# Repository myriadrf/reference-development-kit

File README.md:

# Myriad-RF Hardware

This repository contains the [Myriad-RF](http://myriadrf.org/) reference hardware designs for Lime Microsystem's LMS6002D and LMS7002M transceivers, plus LMS8001 up/down converter, in PDF and [KiCad](http://www.kicad.org) formats, along with the associated firmware.

## Contents

The directory structure for the hardware designs is as follows:

      docs/                      - platform documentation

      <project>/hardware/<version>/
          BOM/                   - bill of materials spreadsheet
          Gerbers/               - Gerber CAM files
          KiCAD/                 - KiCAD schematic and layout files
          Manufacturing/         - Additional manufacturing information
          PDF/                   - Schematic and layout PDFs
          Reports/               - DRC, ERC and drill reports

### Documentation

* RFDIO Connector Specification

The Myriad-RF Radio Frequency Digital Input Output (RFDIO) connector specification defines the electrical and mechanical properties of a high speed card interface for Field Programmable Gate Array (FPGA) based carrier boards. This specification ensures interoperability between carrier (mother) boards and add-on (daughter) RF cards.

*Please note that this needs to be updated with details of the connector specification used by the micro series of boards.*

### Myriad-RF 1 module (myriadrf-1)

Hardware design files for the LMS6002-based Myriad-RF 1 RF module.

Note that there are two versions of the design: one with vias in pads, and another with them off.

### DE0-Nano Interface (de0nano-interface)

Hardware design files and firmware sources (FPGA HDL + Cypress FX2 code) for the DE0-Nano interface that is used with the original Myriad-RF 1 module.

### Zipper Interface (zipper)

This interface allows the Myriad-RF 1 to be used with FPGA development boards that have either a HSMC or FMC connector.

*Note that v1 of the hardware design was not made generally available.*

### uMyriadRF-6002 (umyriadrf-6002)

LMS6002 version of the micro form factor RF module.

### uMyriadRF-7002 (umyriadrf-7002)

LMS7002 version of the micro form factor RF module.

### MyriadRF-8001 (myriadrf-8001)

LMS8001 Companion.

## Licensing

### Hardware

The hardware designs are licensed under a Creative Commons Attribution 3.0 Unported licence.

*Note: The Myriad-RF 1 and DE0-Nano Interface hardware designs were initially published under the Creative Commons Attribution-ShareAlike 3.0 Unported licence. As of 30th September 2013 these have been re-licensed under the more permissive Creative Commons Attribution 3.0 Unported licence.*

### Firmware

For details of firmware licensing please see the associated COPYING file(s).

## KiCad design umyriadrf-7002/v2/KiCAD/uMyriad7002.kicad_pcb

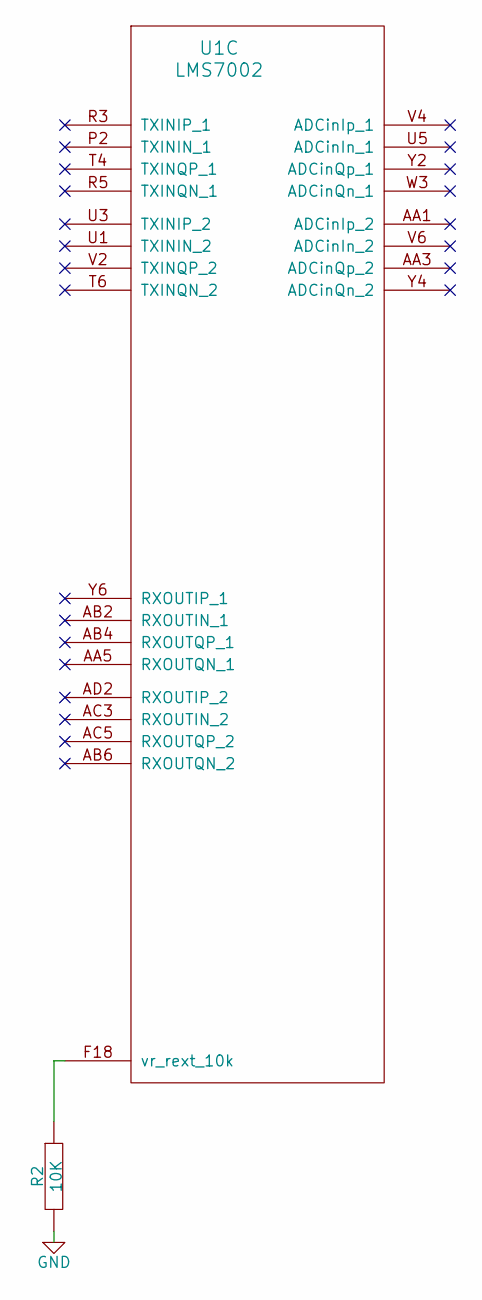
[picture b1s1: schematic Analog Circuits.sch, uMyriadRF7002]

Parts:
R2: 10K_0402; SMD0402; Manufacturer Part Number RMCF0402FT10K0
U1: LMS7002; aQFN-261

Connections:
GND: R2.2; also elsewhere on the board
unnamed: R2.1, U1.F18 (vr_rext_10k)

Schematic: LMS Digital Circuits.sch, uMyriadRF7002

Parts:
C13, C14, C15: 1UF_0402; SMD0402; Manufacturer Part Number CC0402ZRY5V5BB105
C22: 10PF_0402; SMD0402; Manufacturer Part Number CC0402JRNPO9BN100
J1: 100-PIN_CONNECTOR_3MMHEIGHT; 100-PIN_CONNECTOR; Manufacturer Part Number DF40HC(3.0)-100DS-0.4V(58)
R1, R11, R19, R20, R21, R22, R24: 10K_0402; SMD0402; Manufacturer Part Number RMCF0402FT10K0
R25, R26, R27, R28: 47R_0402; SMD0402; Manufacturer Part Number RC0402FR-0747RL
R29, R39: 2K2_0402; SMD0402; Manufacturer Part Number RC0402FR-072K2L
U1: LMS7002; aQFN-261
U6: 24FC512; 8-TSSOP; Manufacturer Part Number 24FC512-I/ST
U8: 24FC64F; 8-TSSOP; Manufacturer Part Number 24FC64F-I/ST

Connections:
+1.8V: J1.21, J1.22, J1.23, J1.24; also elsewhere on the board
+1.25V: J1.83, J1.84, J1.85, J1.86; also elsewhere on the board
+3.3V: C13.1, C14.1, C15.1, J1.17, J1.18, J1.19, J1.20, R11.1, R19.1, R20.1, R22.1, R24.1, R29.1, R39.1, U6.1 (A0), U6.2 (A1), U6.3 (A2), U6.8 (Vcc), U8.8 (Vcc); also elsewhere on the board
DIG_RST: J1.44, R21.2, U1.V30 (DIG_RST)
DIQ1_D0: J1.74, U1.AG31 (DIQ0_1)
DIQ1_D1: J1.76, U1.AF30 (DIQ1_1)
DIQ1_D2: J1.79, U1.AF34 (DIQ2_1)
DIQ1_D3: J1.72, U1.AE31 (DIQ3_1)
DIQ1_D4: J1.70, U1.AD30 (DIQ4_1)
DIQ1_D5: J1.78, U1.AC29 (DIQ5_1)
DIQ1_D6: J1.77, U1.AE33 (DIQ6_1)
DIQ1_D7: J1.75, U1.AD32 (DIQ7_1)
DIQ1_D8: J1.68, U1.AC31 (DIQ8_1)
DIQ1_D9: J1.73, U1.AC33 (DIQ9_1)
DIQ1_D10: J1.80, U1.AB30 (DIQ10_1)
DIQ1_D11: J1.66, U1.AB32 (DIQ11_1)
DIQ2_D0: J1.52, U1.H30 (DIQ0_2)
DIQ2_D1: J1.49, U1.J31 (DIQ1_2)
DIQ2_D2: J1.50, U1.K30 (DIQ2_2)
DIQ2_D3: J1.51, U1.K32 (DIQ3_2)
DIQ2_D4: J1.56, U1.L31 (DIQ4_2)
DIQ2_D5: J1.54, U1.K34 (DIQ5_2)
DIQ2_D6: J1.58, U1.M30 (DIQ6_2)
DIQ2_D7: J1.53, U1.M32 (DIQ7_2)
DIQ2_D8: J1.60, U1.N31 (DIQ8_2)
DIQ2_D9: J1.55, U1.N33 (DIQ9_2)
DIQ2_D10: J1.64, U1.P30 (DIQ10_2)
DIQ2_D11: J1.62, U1.P32 (DIQ11_2)
ENABLE_IQSEL1: J1.67, U1.Y32 (IQSEL_Enable_1)
ENABLE_IQSEL2: J1.59, U1.R33 (IQSEL_Enable_2)
FCLK1: J1.69, U1.AA33 (FCLK1)
FCLK2: J1.61, U1.R29 (FCLK_2)
FPGA_LMS_CS: J1.38, R25.2
FPGA_SPI_MISO: J1.37, R28.2
FPGA_SPI_MOSI: J1.36, R27.2
FPGA_SPI_SCK: J1.40, R26.2
GND: C13.2, C14.2, C15.2, C22.2, J1.1, J1.2, J1.3, J1.4, J1.5, J1.6, J1.7, J1.8, J1.9, J1.10, J1.15, J1.16, J1.25, J1.26, J1.27, J1.28, J1.29, J1.30, J1.31, J1.32, J1.33, J1.34, J1.81, J1.82, J1.87, J1.88, J1.90, J1.91, J1.92, J1.93, J1.94, J1.95, J1.96, J1.97, J1.98, J1.99, J1.100, R1.1, R21.1, U6.4 (Vss), U6.7 (WP), U8.1 (A0), U8.2 (A1), U8.3 (A2), U8.4 (Vss), U8.7 (WP); also elsewhere on the board
GPIOn: J1.43; also elsewhere on the board
GPIOp: J1.41; also elsewhere on the board
G_PWR_DWN: J1.46, R24.2, U1.U33 (G_PWR_DWN)
MCLK1: J1.71, U1.AB34 (MCLK1)
MCLK2: J1.57, U1.P34 (MCLK_2)
unnamed: R25.1, U1.D28 (SEN)
unnamed: R28.1, U1.F28 (SDO)
unnamed: R27.1, U1.F30 (SDIO)
unnamed: C22.1, R26.1, U1.C29 (SCLK)
unnamed: R29.2, U1.D26 (SDA), U6.5 (SDA), U8.5 (SDA)
unnamed: R39.2, U1.C27 (SCL), U6.6 (SCL), U8.6 (SCL)
RESET: J1.42, R22.2, U1.E27 (RESET)
RXPLL_CLK: J1.89, U1.AM24 (RxPLL_CLK)
RX_EN: J1.47, R11.2, U1.V34 (RX_EN)
TXNRX1: J1.65, R19.2, U1.V32 (TXNRX1)
TXNRX2: J1.63, R1.2, U1.U31 (TXNRX2)
TXPLL_CLK: J1.35, U1.E5 (TxPLL_CLK)
TX_EN: J1.48, R20.2, U1.U29 (TX_EN)

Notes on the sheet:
+5V

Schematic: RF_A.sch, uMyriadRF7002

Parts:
C1, C2, C16, C220, C221: 100NF_0402; SMD0402; Manufacturer Part Number CC0402ZRY5V7BB104
C3, C7, C32: 1PF_0402; SMD0402; Manufacturer Part Number C1005C0G1H010B050BA
C6: 0.5PF_0402_NF; SMD0402; Manufacturer Part Number CC0402CRNPO9BNR50
C9, C10: 4.7PF_0402; SMD0402; Manufacturer Part Number GRM1555C1H4R7BA01D
C17, C222: 22PF_0402; SMD0402; Manufacturer Part Number CC0402JRNPO9BN220
C33, C218, C219, C223: 100PF_0402; SMD0402; Manufacturer Part Number CC0402JRNPO9BN101
EK1: SHIELD_30X25MM; shield_30x25mm
L3, L9: 12NH_0402_NF; IND_0402; Manufacturer Part Number 0402HP-12NX_LU
L4: 3.9NH_0402; IND_0402; Manufacturer Part Number 0402HP-3N9XGLU
L7, L8: 8.2NH_0402; IND_0402; Manufacturer Part Number 0402HP-8N2XJLU
R9, R12: 0R_0805; SM0805; Manufacturer Part Number RC0805JR-070RL
R44: 10K_0402; SMD0402; Manufacturer Part Number RMCF0402FT10K0
T1, T2: TR_TCM1-63AX+; TCM1-63AX+; Manufacturer Part Number TCM1-63AX+
T5: TR_TC1; TC1-1-13MA+; Manufacturer Part Number TC1-1-13MA+
U1: LMS7002; aQFN-261; Manufacturer Part Number LMS7002M
U7: PE4245; 6-DFN_PE4245; Manufacturer Part Number 4245-52
X1, X3: U.FL; Manufacturer Part Number 0734120110

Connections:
+1.8V: C1.1, C2.1, R9.1, R12.1; also elsewhere on the board
+3.3V: C16.1, C17.1, C221.1, C222.1, L9.1, R44.2, U7.4 (Vdd3V); also elsewhere on the board
GND: C1.2, C2.2, C16.2, C17.2, C220.2, C221.2, C222.2, EK1.1, T1.1, T1.2, T1.5, T2.1, T2.2, T2.5, T5.2, T5.4, T5.5, U1.AK12 (RF_gnd), U1.AL13 (RF_gnd), U7.2 (GND), X1.2 (GND), X3.2 (GND); also elsewhere on the board
GPIOp: C220.1, R44.1, U7.5 (CTRL); also elsewhere on the board
unnamed: C218.2, U7.3 (RF1)
unnamed: C223.1, U7.6 (RFC)
unnamed: C218.1, T5.6
unnamed: C3.2, C7.1, T1.4
unnamed: C7.2, C32.2, T1.6
unnamed: C219.1, T2.3
unnamed: C219.2, U7.1 (RF2)
unnamed: C223.2, L9.2, X1.1 (RF)
unnamed: L7.1, R9.2
unnamed: L8.1, R12.2
unnamed: C33.1, T1.3
unnamed: C9.1, L3.1, U1.AK14 (RXRF1_p_h)
unnamed: C10.1, L3.2, U1.AJ15 (RXRF1_n_h)
unnamed: C9.2, L4.1, T2.4
unnamed: C10.2, L4.2, T2.6
unnamed: C6.2, C32.1, L8.2, U1.A7 (TXRF1_1n)
unnamed: C33.2, X3.1 (RF)
unnamed: C3.1, C6.1, L7.2, U1.B8 (TXRF1_1p)
unnamed: T5.3, U1.AM12 (RXRF1_n_l)
unnamed: T5.1, U1.AN11 (RXRF1_p_l)

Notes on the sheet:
TXOUT_A
GPIO 0 - RF1 1 - RF2
RXIN_A

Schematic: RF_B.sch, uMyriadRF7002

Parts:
C11, C12: 4.7PF_0402; SMD0402; Manufacturer Part Number GRM1555C1H4R7BA01D
C18, C38, C39, C233, C234: 100NF_0402; SMD0402; Manufacturer Part Number CC0402ZRY5V7BB104
C19, C235: 22PF_0402; SMD0402; Manufacturer Part Number CC0402JRNPO9BN220
C40, C42, C43: 1PF_0402; SMD0402; Manufacturer Part Number C1005C0G1H010B050BA
C41: 0.5PF_0402_NF; SMD0402; Manufacturer Part Number CC0402CRNPO9BNR50
C45, C231, C232, C236: 100PF_0402; SMD0402; Manufacturer Part Number CC0402JRNPO9BN101
EK2: SHIELD_30X25MM; shield_30x25mm
L5, L14: 12NH_0402_NF; IND_0402; Manufacturer Part Number 0402HP-12NX_LU
L6: 3.9NH_0402; IND_0402; Manufacturer Part Number 0402HP-3N9XGLU
L12, L13: 8.2NH_0402; IND_0402; Manufacturer Part Number 0402HP-8N2XJLU
R13, R14: 0R_0805; SM0805; Manufacturer Part Number RC0805JR-070RL
R45: 10K_0402; SMD0402; Manufacturer Part Number RMCF0402FT10K0
T3, T4: TR_TCM1-63AX+; TCM1-63AX+; Manufacturer Part Number TCM1-63AX+
T6: TR_TC1; TC1-1-13MA+; Manufacturer Part Number TC1-1-13MA+
U1: LMS7002; aQFN-261
U9: PE4245; 6-DFN_PE4245; Manufacturer Part Number 4245-52
X2, X4: U.FL; Manufacturer Part Number 0734120110

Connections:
+1.8V: C38.1, C39.1, R13.1, R14.1; also elsewhere on the board
+3.3V: C18.1, C19.1, C234.1, C235.1, L14.1, U9.4 (Vdd3V); also elsewhere on the board
GND: C18.2, C19.2, C38.2, C39.2, C233.2, C234.2, C235.2, EK2.1, R45.2, T3.1, T3.2, T3.5, T4.1, T4.2, T4.5, T6.2, T6.4, T6.5, U1.AJ7 (RF_gnd), U1.AJ9 (RF_gnd), U9.2 (GND), X2.2 (GND), X4.2 (GND); also elsewhere on the board
GPIOn: C233.1, R45.1, U9.5 (CTRL); also elsewhere on the board
unnamed: C231.1, T6.6
unnamed: C231.2, U9.1 (RF2)
unnamed: C232.2, U9.3 (RF1)
unnamed: T6.3, U1.AN5 (RXRF2_l_p)
unnamed: C236.1, U9.6 (RFC)
unnamed: C236.2, L14.2, X2.1 (RF)
unnamed: C12.2, L6.2, T4.4
unnamed: C42.2, C43.2, T3.6
unnamed: C45.1, T3.3
unnamed: C232.1, T4.3
unnamed: C11.1, L5.1, U1.AN7 (RXRF2_h_p)
unnamed: C12.1, L5.2, U1.AM8 (RXRF2_h_n)
unnamed: C11.2, L6.1, T4.6
unnamed: T6.1, U1.AP6 (RXRF2_l_n)
unnamed: L13.1, R14.2
unnamed: L12.1, R13.2
unnamed: C41.2, C43.1, L13.2, U1.C11 (TXRF1_2n)
unnamed: C45.2, X4.1 (RF)
unnamed: C40.2, C42.1, T3.4
unnamed: C40.1, C41.1, L12.2, U1.B12 (TXRF1_2p)

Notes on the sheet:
TXOUT_B
GPIO 0 - RF1 1 - RF2
RXIN_B

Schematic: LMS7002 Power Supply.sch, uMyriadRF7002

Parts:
C4, C8: 1UF_0402; SMD0402; Manufacturer Part Number CC0402ZRY5V5BB105
C35, C47, C50, C51, C52, C53, C54, C55, C56, C57, C58, C59, C60, C61, C62, C63, C65, C66, C67, C68, C69, C111, C145, C154, C167, C173, C175, C195, C197, C204, C205, C206, C207, C208, C209, C210, C211, C212, C213, C214, C255, C283, C301, C302, C303, C304: 1UF_0201; SM0201; Manufacturer Part Number C0603X5R0J105M030BC
FB1, FB2, FB3, FB4, FB5, FB6, FB7, FB8, FB9, FB10, FB11, FB12, FB13, FB14, FB15, FB16, FB17, FB18, FB19, FB22, FB24: FB_0201; SM0201; Manufacturer Part Number BK0603TS601-T
FB23, FB25: FB_0201_NF; SM0201; Manufacturer Part Number BK0603TS601-T
FD1, FD2, FD3, FD4: FIDUCIAL; Pad
LD1: LED; LED_0603; Manufacturer Part Number LG Q971-KN-1
R3, R4: 0.22R_0402; SMD0402; Manufacturer Part Number RL0402FR-070R22L
R5, R6, R40, R43: 0R_0201; SMD0201; Manufacturer Part Number MCR006YRTJ000
R7, R17, R23, R33, R41, R42: 10R_0201; SMD0201; Manufacturer Part Number RC0201JR-0710RP
R8: 0R_0402; SMD0402; Manufacturer Part Number RC0402JR-070RL
R10: 470R_0402; SMD0402; Manufacturer Part Number ERA-2AED471X
U1: LMS7002; aQFN-261
U2: LD39115J14R; 4-UFBGA; Manufacturer Part Number LD39115J14R

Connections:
+1.4V: FB5.2, FB15.2, FB18.2, FB23.2, FB25.1, R8.1
+1.8V: FB3.2, FB6.1, FB7.2, FB14.1, FB16.2, FB17.1, R5.2; also elsewhere on the board
+1.25V: C60.2, C63.1, C66.2, C69.1, C173.1, C175.2, FB1.1, FB2.2, FB4.2, FB8.2, FB9.1, FB10.2, FB11.2, FB12.1, FB13.2, FB19.1, FB22.1, FB24.1, R3.2, R7.2, R17.1, R23.2, R33.1, R41.1, R42.2; also elsewhere on the board
+3.3V: C4.1, R4.1, R10.1, U2.A2 (EN), U2.B2 (IN); also elsewhere on the board
/LMS7002 Power Supply/RF Power 1: C58.1, C302.1, FB2.1, R6.1, R40.1, U1.B16 (VDD_TPAD_TRF), U1.F8 (VDD_TLOBUF_TRF), U1.K6 (VDD12_VCO_SXT)
/LMS7002 Power Supply/RF Power 2: C283.2, FB22.2, U1.AN23 (VDD12_VCO_SXR)
GND: C4.2, C8.2, C35.1, C47.1, C50.1, C51.1, C52.1, C53.1, C54.1, C55.1, C56.2, C57.1, C58.2, C59.2, C60.1, C61.1, C62.2, C63.2, C65.2, C66.1, C67.1, C68.2, C69.2, C111.2, C145.1, C154.2, C167.2, C173.2, C175.1, C195.1, C197.2, C204.1, C205.2, C206.2, C207.1, C208.2, C209.1, C210.2, C211.2, C212.1, C213.2, C214.1, C255.2, C283.1, C301.2, C302.2, C303.2, C304.1, LD1.2 (K), U1.AA31 (DIGPRGND1), U1.AF32 (DIGPRGND2), U1.AG29 (DIGPRGND1), U1.AJ19 (GND_CP_SXR), U1.AK20 (GND_DIV_SXR), U1.AL23 (GND_VCO_SXR), U1.AM22 (DGND_SXR), U1.AN25 (GND_RXBUF), U1.B18 (DGND_CGEN), U1.B20 (GND_CP_CGEN), U1.C7 (GND_TLOBUF_TRF), U1.C23 (GND_DIG), U1.D20 (GND_DIV_CGEN), U1.E25 (GND_SPI_BUF), U1.F6 (GND_TXBUF), U1.G31 (DIGPRGND2), U1.GND (GND_TPAD_TRF), U1.H2 (GND_VCO_SXT), U1.J33 (DIGPRGND1), U1.K4 (GND_CP_SXT), U1.L3 (GND_DIV_SXT), U1.N3 (DGND_SXT), U1.T30 (DIGPRGND1), U1.W29 (DIGPRGND1), U1.Y30 (DIGPRGND2), U2.A1 (GND); also elsewhere on the board
unnamed: C167.1, R41.2, U1.AL19 (VDD_CP_SXR)
unnamed: C197.1, FB8.1, U1.AM20 (VDD_DIV_SXR)
unnamed: C213.1, FB18.1, U1.AD4 (VDD14_RBB)
unnamed: C62.1, R17.2, U1.A17 (DVDD_CGEN)
unnamed: C154.1, FB7.1, U1.AM18 (VDD18_SXR)
unnamed: C205.1, FB10.1, FB23.1, U1.AN17 (VDD_MXLOBUF_RFE)
unnamed: C208.1, FB13.1, U1.AP26 (VDD12_RXBIF)
unnamed: C211.1, C255.1, FB16.1, U1.AK22 (VDD18_VCO_SXR), U1.AM26 (VDD18_RXBUF)
unnamed: C59.1, C303.1, FB3.1, U1.D16 (VDD18_TRF), U1.E17 (VDD18_BIAS), U1.E21 (VDD18_VCO_CGEN)
unnamed: C111.1, FB5.1, U1.C21 (VDD14_VCO_CGEN)
unnamed: C210.1, FB15.1, U1.AF2 (VDD14_TIA_RFE), U1.AF6 (VDD14_LNA_RFE)
unnamed: C206.1, FB11.1, U1.AJ25 (VDD_AFE)
unnamed: R6.2, U1.D6 (VDDO_TLOBUF_TRF)
unnamed: C65.1, FB4.1, U1.E19 (VDD_DIV_CGEN)
unnamed: C8.1, R8.2, U2.B1 (OUT)
unnamed: LD1.1 (A), R10.2
unnamed: C68.1, R33.2, U1.F20 (VDD_CP_CGEN)
unnamed: C47.2, C53.2, C54.2, C55.2, R4.2, U1.AH30 (DIGPRVDD2), U1.H32 (DIGPRVDD2), U1.T32 (DIGPRVDD2), U1.W31 (DIGPRPOC), U1.W33 (DIGPRVDD2)
unnamed: C212.2, FB17.2, U1.AE3 (VDD18_TIA_RFE), U1.AF4 (VDD18_LDO_RX)
unnamed: C209.2, FB14.2, U1.N1 (VDD18_LDO_TX)
unnamed: C214.2, FB19.2, U1.AD6 (VDD12_TIA_RFE), U1.AG5 (VDD12_LNA_RFE)
unnamed: C56.1, R5.1, U1.D24 (VDD18_DIG)
unnamed: C207.2, FB12.2, U1.G5 (VDD12_TXBUF)
unnamed: C57.2, C304.2, FB1.2, U1.C25 (VDD12_DIG), U1.F24 (VDD_SPI_BUF)
unnamed: C35.2, C50.2, C51.2, C52.2, R3.1, U1.AA29 (DIGPRVDD1), U1.AE29 (DIGPRVDD1), U1.L33 (DIGPRVDD1), U1.R31 (DIGPRVDD1)
unnamed: C301.1, FB24.2, U1.P4 (VDD_TBB)
unnamed: R43.1, U1.K2 (VDDO_DIV_SXT)
unnamed: R40.2, U1.J5 (VDD12O_VCO_SXT)
unnamed: C145.2, FB6.2, U1.G3 (VDD18_VCO_SXT), U1.H6 (VDD18_TXBUF)
unnamed: C67.2, R23.1, U1.M4 (DVDD_SXT)
unnamed: C61.2, R7.1, U1.AL21 (DVDD_SXR)
unnamed: C195.2, R42.1, U1.J3 (VDD_CP_SXT)
unnamed: C204.2, FB9.2, FB25.2, R43.2, U1.L5 (VDD_DIV_SXT)

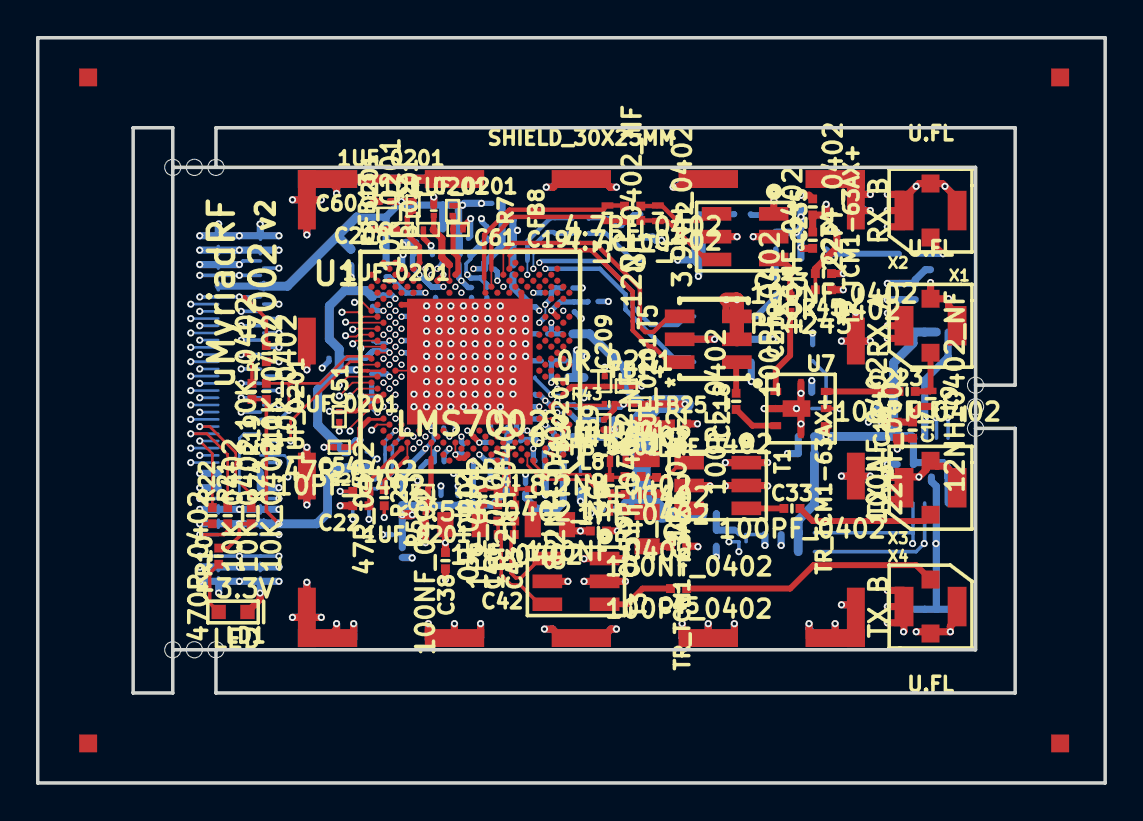
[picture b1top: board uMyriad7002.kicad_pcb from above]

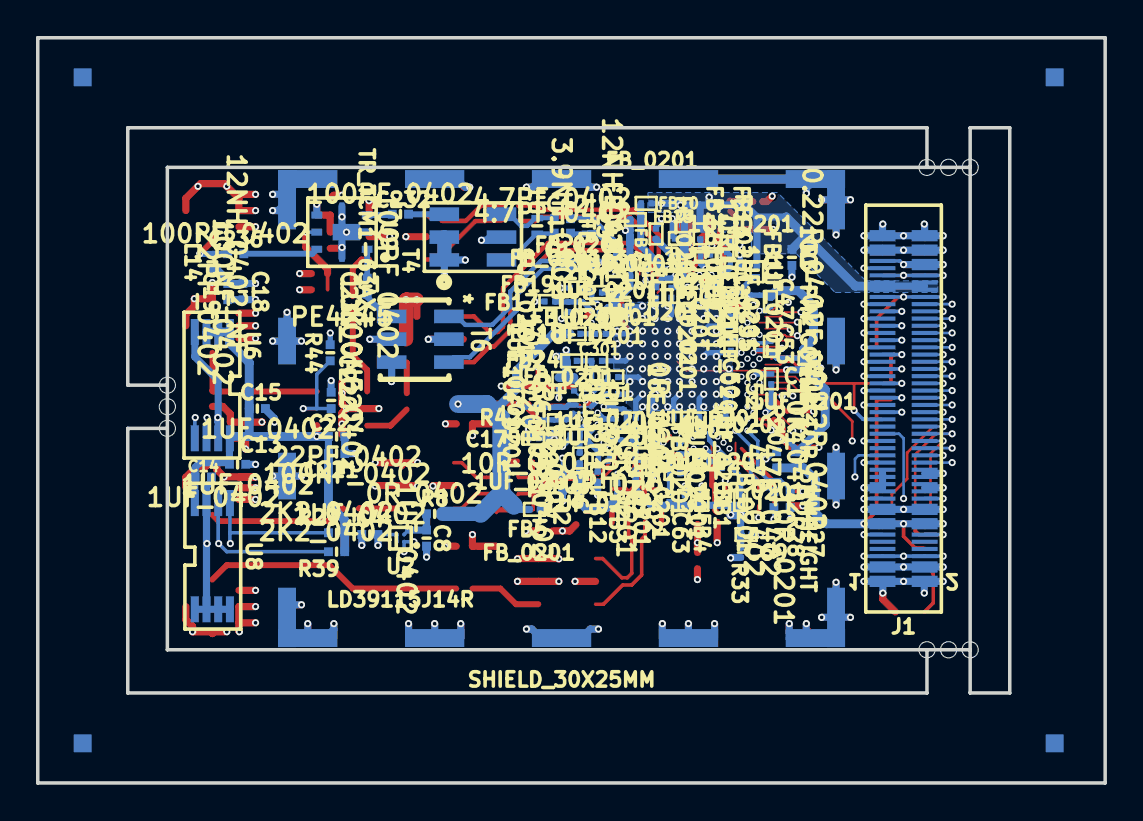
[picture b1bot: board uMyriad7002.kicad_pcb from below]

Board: 8 copper layers, 59.3 x 41.4 mm, 186 parts (99 on the bottom side), 132 nets.

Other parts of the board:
BreakHole: VAL**; BreakHole
BreakHole#2, BreakHole#3, BreakHole#4, BreakHole#5, BreakHole#6, BreakHole#7, BreakHole#8, BreakHole#9: VAL**; BreakHole

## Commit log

2015-12-03 Added micro form factor LMS6002 and LMS7002 RF module designs
2016-06-17 Added LMS8001 Companion design
2021-11-10 Update README.md
    https://forum.kicad.info/t/warning-avoid-all-links-to-kicad-pcb-org-use-kicad-org/31521

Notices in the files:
umyriadrf-6002/v2/KiCAD/LMS Digital Circuits.sch:
THIS WORK IS COVERED UNDER A CREATIVE COMMONS LICENSE (CC BY 3.0)
